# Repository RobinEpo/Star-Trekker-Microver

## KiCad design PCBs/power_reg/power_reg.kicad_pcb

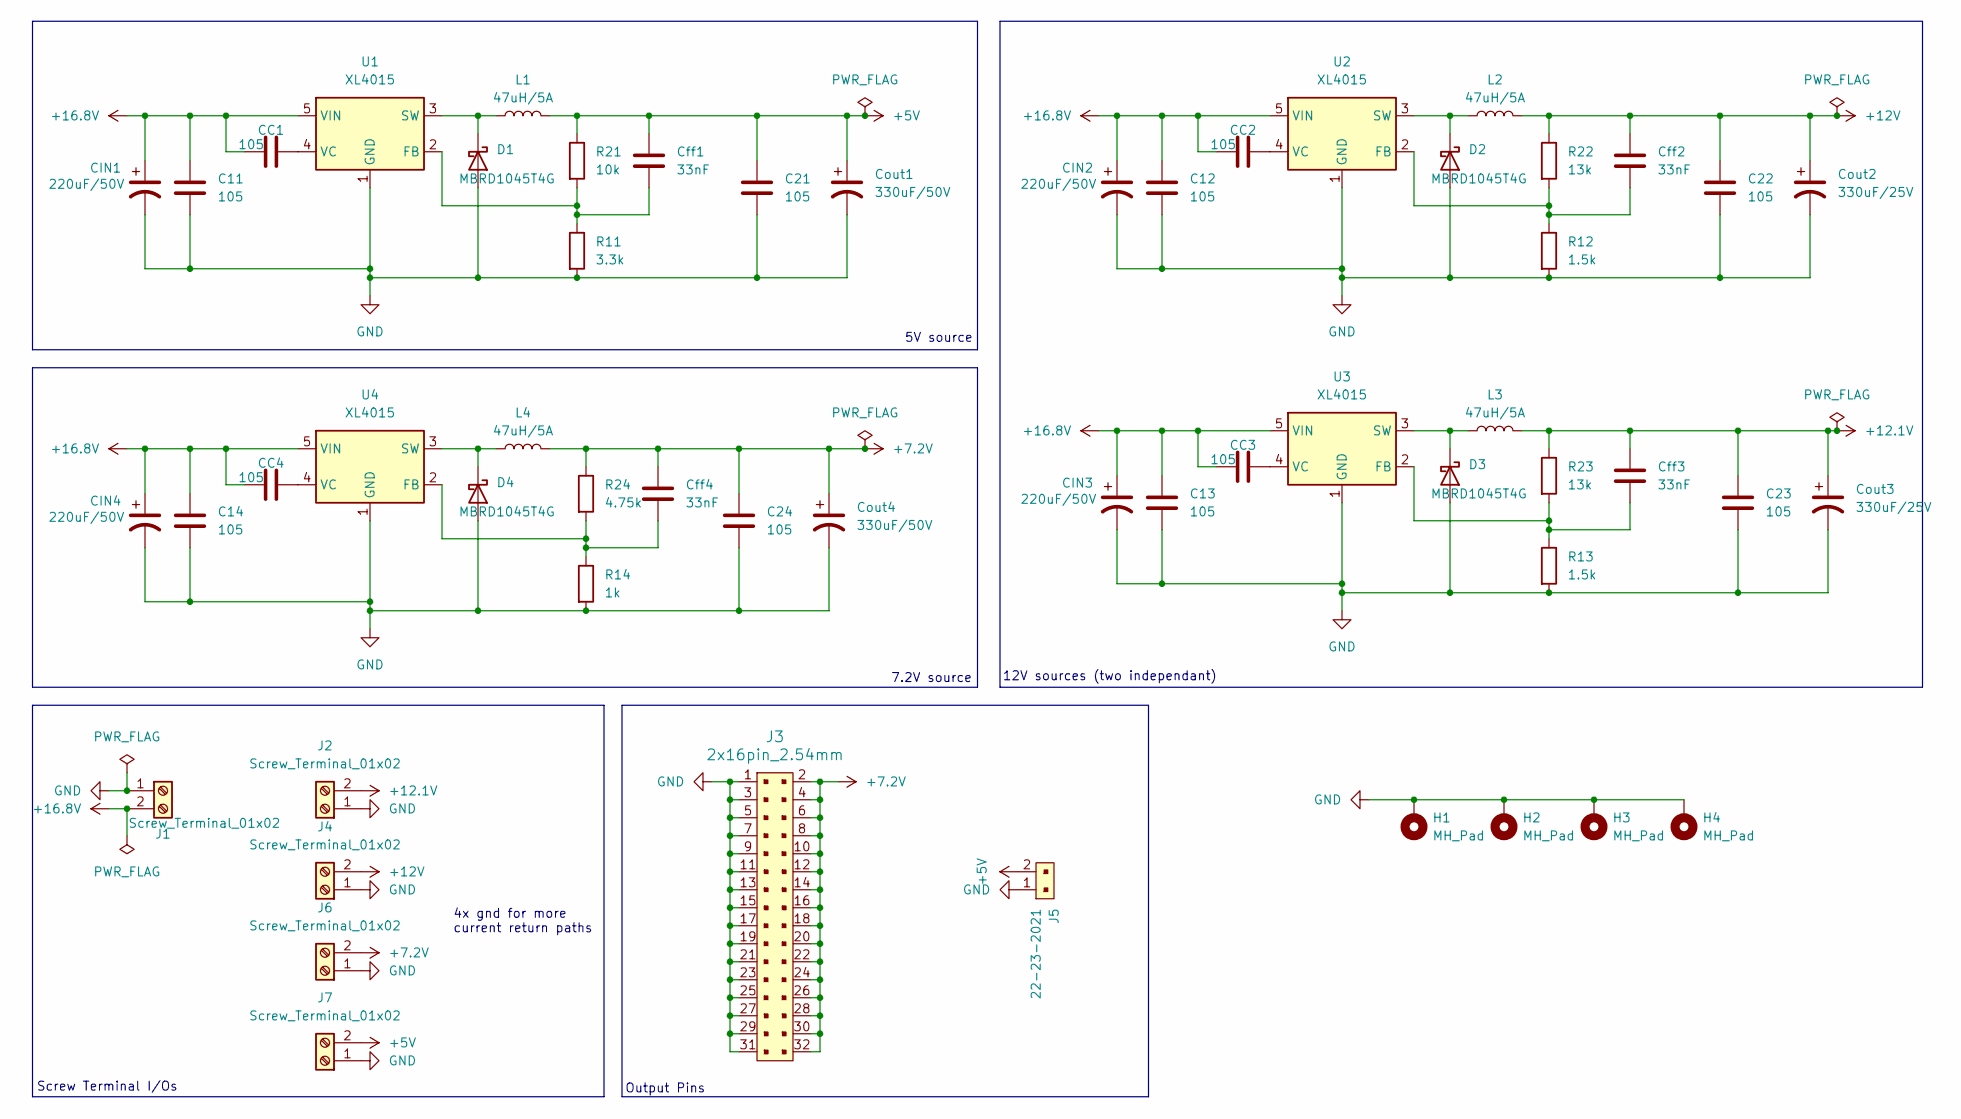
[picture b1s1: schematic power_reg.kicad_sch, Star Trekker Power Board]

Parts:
C11, C12, C13, C14, C21, C22, C23, C24: 105; C_0805_2012Metric_Pad1.18x1.45mm_HandSolder
CC1, CC2, CC3, CC4: 105; C_0805_2012Metric_Pad1.18x1.45mm_HandSolder
CIN1, CIN2, CIN3, CIN4: 220uF/50V; CP_Elec_10x10.5
Cff1, Cff2, Cff3, Cff4: 33nF; C_0603_1608Metric_Pad1.08x0.95mm_HandSolder
Cout1, Cout4: 330uF/50V; CP_Elec_10x10.5
Cout2, Cout3: 330uF/25V; CP_Elec_10x10.5
D1, D2, D3, D4: MBRD1045T4G; TO-252-2
H1, H2, H3, H4: MH_Pad; MountingHole_3.2mm_M3_DIN965_Pad
J1, J2, J4, J6, J7: Screw_Terminal_01x02; TerminalBlock_Phoenix_PT-1,5-2-5.0-H_1x02_P5.00mm_Horizontal
J3: 2x16pin_2.54mm; PinHeader_2x16_P2.54mm_Vertical; MPN 3220-10-0100-00; Digi-Key_PN 1175-1627-ND
J5: 22-23-2021; PinHeader_1x2_P2.54mm_Drill1.02mm; MPN 22-23-2021; Digi-Key_PN WM4200-ND
L1, L2, L3, L4: 47uH/5A; L_13.8x12.6mm_H6.5mm
R11: 3.3k; R_0805_2012Metric_Pad1.20x1.40mm_HandSolder
R12, R13: 1.5k; R_0805_2012Metric_Pad1.20x1.40mm_HandSolder
R14: 1k; R_0805_2012Metric_Pad1.20x1.40mm_HandSolder
R21: 10k; R_0805_2012Metric_Pad1.20x1.40mm_HandSolder
R22, R23: 13k; R_0805_2012Metric_Pad1.20x1.40mm_HandSolder
R24: 4.75k; R_0805_2012Metric_Pad1.20x1.40mm_HandSolder
U1, U2, U3, U4: XL4015; TO-263-5_TabPin3

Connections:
+5V: C21.1, Cff1.1, Cout1.1, J5.2, J7.2, L1.2, R21.1
+7.2V: C24.1, Cff4.1, Cout4.1, J3.2, J3.4, J3.6, J3.8, J3.10, J3.12, J3.14, J3.16, J3.18, J3.20, J3.22, J3.24, J3.26, J3.28, J3.30, J3.32, J6.2, L4.2, R24.1
+12.1V: C23.1, Cff3.1, Cout3.1, J2.2, L3.2, R23.1
+12V: C22.1, Cff2.1, Cout2.1, J4.2, L2.2, R22.1
+16.8V: C11.1, C12.1, C13.1, C14.1, CC1.1, CC2.1, CC3.1, CC4.1, CIN1.1, CIN2.1, CIN3.1, CIN4.1, J1.2, U1.5 (VIN), U2.5 (VIN), U3.5 (VIN), U4.5 (VIN)
GND: C11.2, C12.2, C13.2, C14.2, C21.2, C22.2, C23.2, C24.2, CIN1.2, CIN2.2, CIN3.2, CIN4.2, Cout1.2, Cout2.2, Cout3.2, Cout4.2, D1.1 (A), D2.1 (A), D3.1 (A), D4.1 (A), H1.1, H2.1, H3.1, H4.1, J1.1, J2.1, J3.1, J3.3, J3.5, J3.7, J3.9, J3.11, J3.13, J3.15, J3.17, J3.19, J3.21, J3.23, J3.25, J3.27, J3.29, J3.31, J4.1, J5.1, J6.1, J7.1, R11.2, R12.2, R13.2, R14.2, U1.1 (GND), U2.1 (GND), U3.1 (GND), U4.1 (GND)
unnamed: D1.2 (K), L1.1, U1.3 (SW)
unnamed: D2.2 (K), L2.1, U2.3 (SW)
unnamed: D3.2 (K), L3.1, U3.3 (SW)
unnamed: D4.2 (K), L4.1, U4.3 (SW)
unnamed: Cff1.2, R11.1, R21.2, U1.2 (FB)
unnamed: CC1.2, U1.4 (VC)
unnamed: Cff2.2, R12.1, R22.2, U2.2 (FB)
unnamed: CC2.2, U2.4 (VC)
unnamed: Cff3.2, R13.1, R23.2, U3.2 (FB)
unnamed: CC3.2, U3.4 (VC)
unnamed: Cff4.2, R14.1, R24.2, U4.2 (FB)
unnamed: CC4.2, U4.4 (VC)

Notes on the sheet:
Output Pins
5V source
Screw Terminal I/Os
7.2V source
12V sources (two independant)
4x gnd for more current return paths

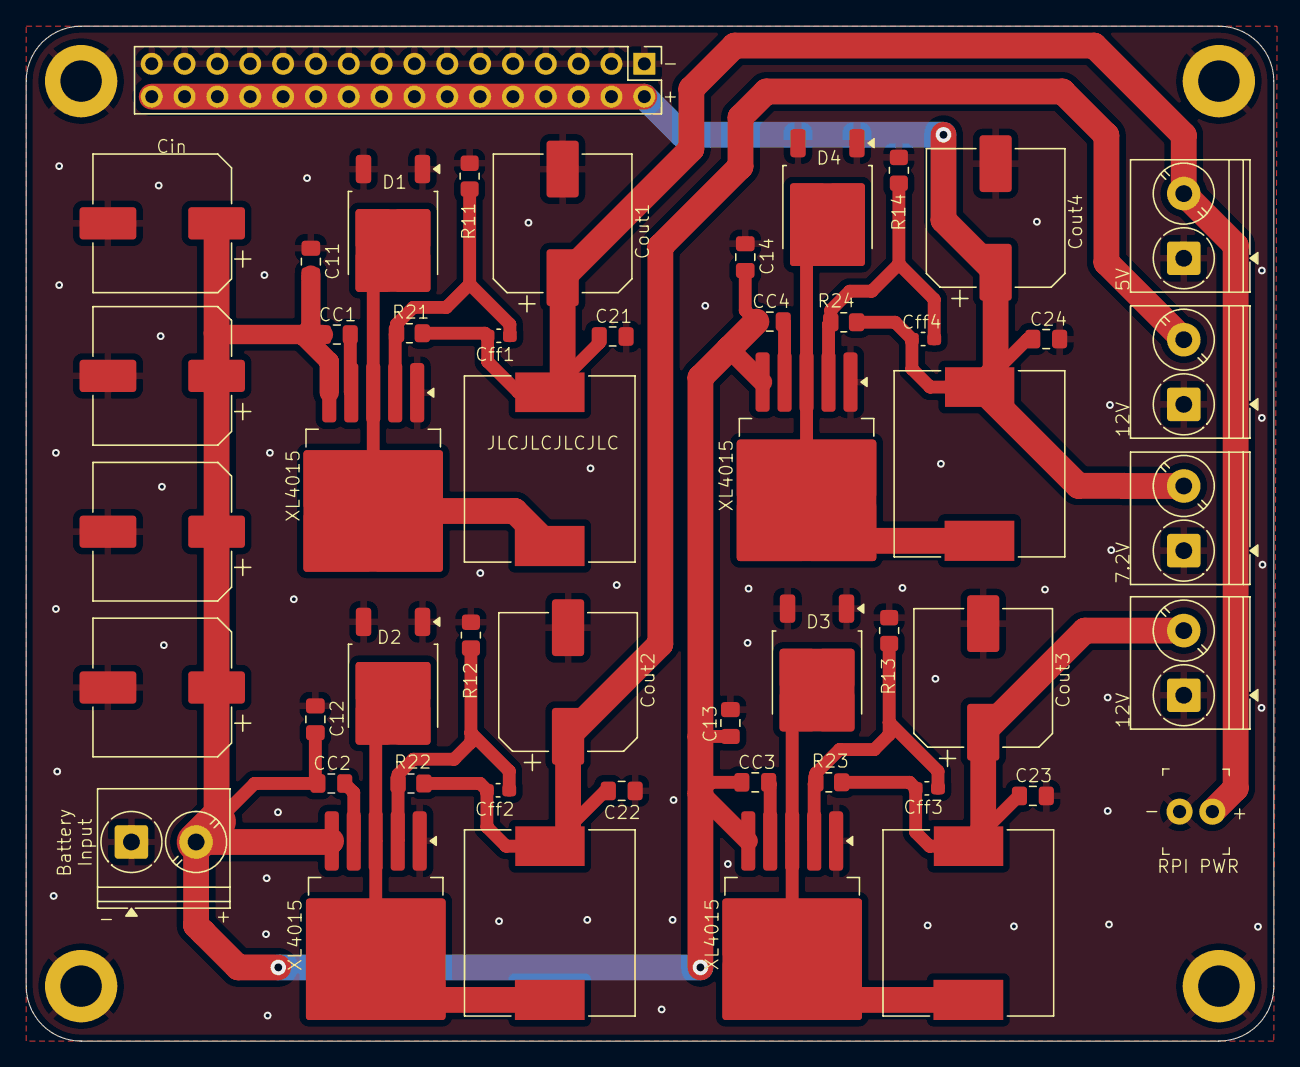
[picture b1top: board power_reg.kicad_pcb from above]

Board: 2 copper layers, 96.5 x 78.5 mm, 55 parts (0 on the bottom side), 18 nets.

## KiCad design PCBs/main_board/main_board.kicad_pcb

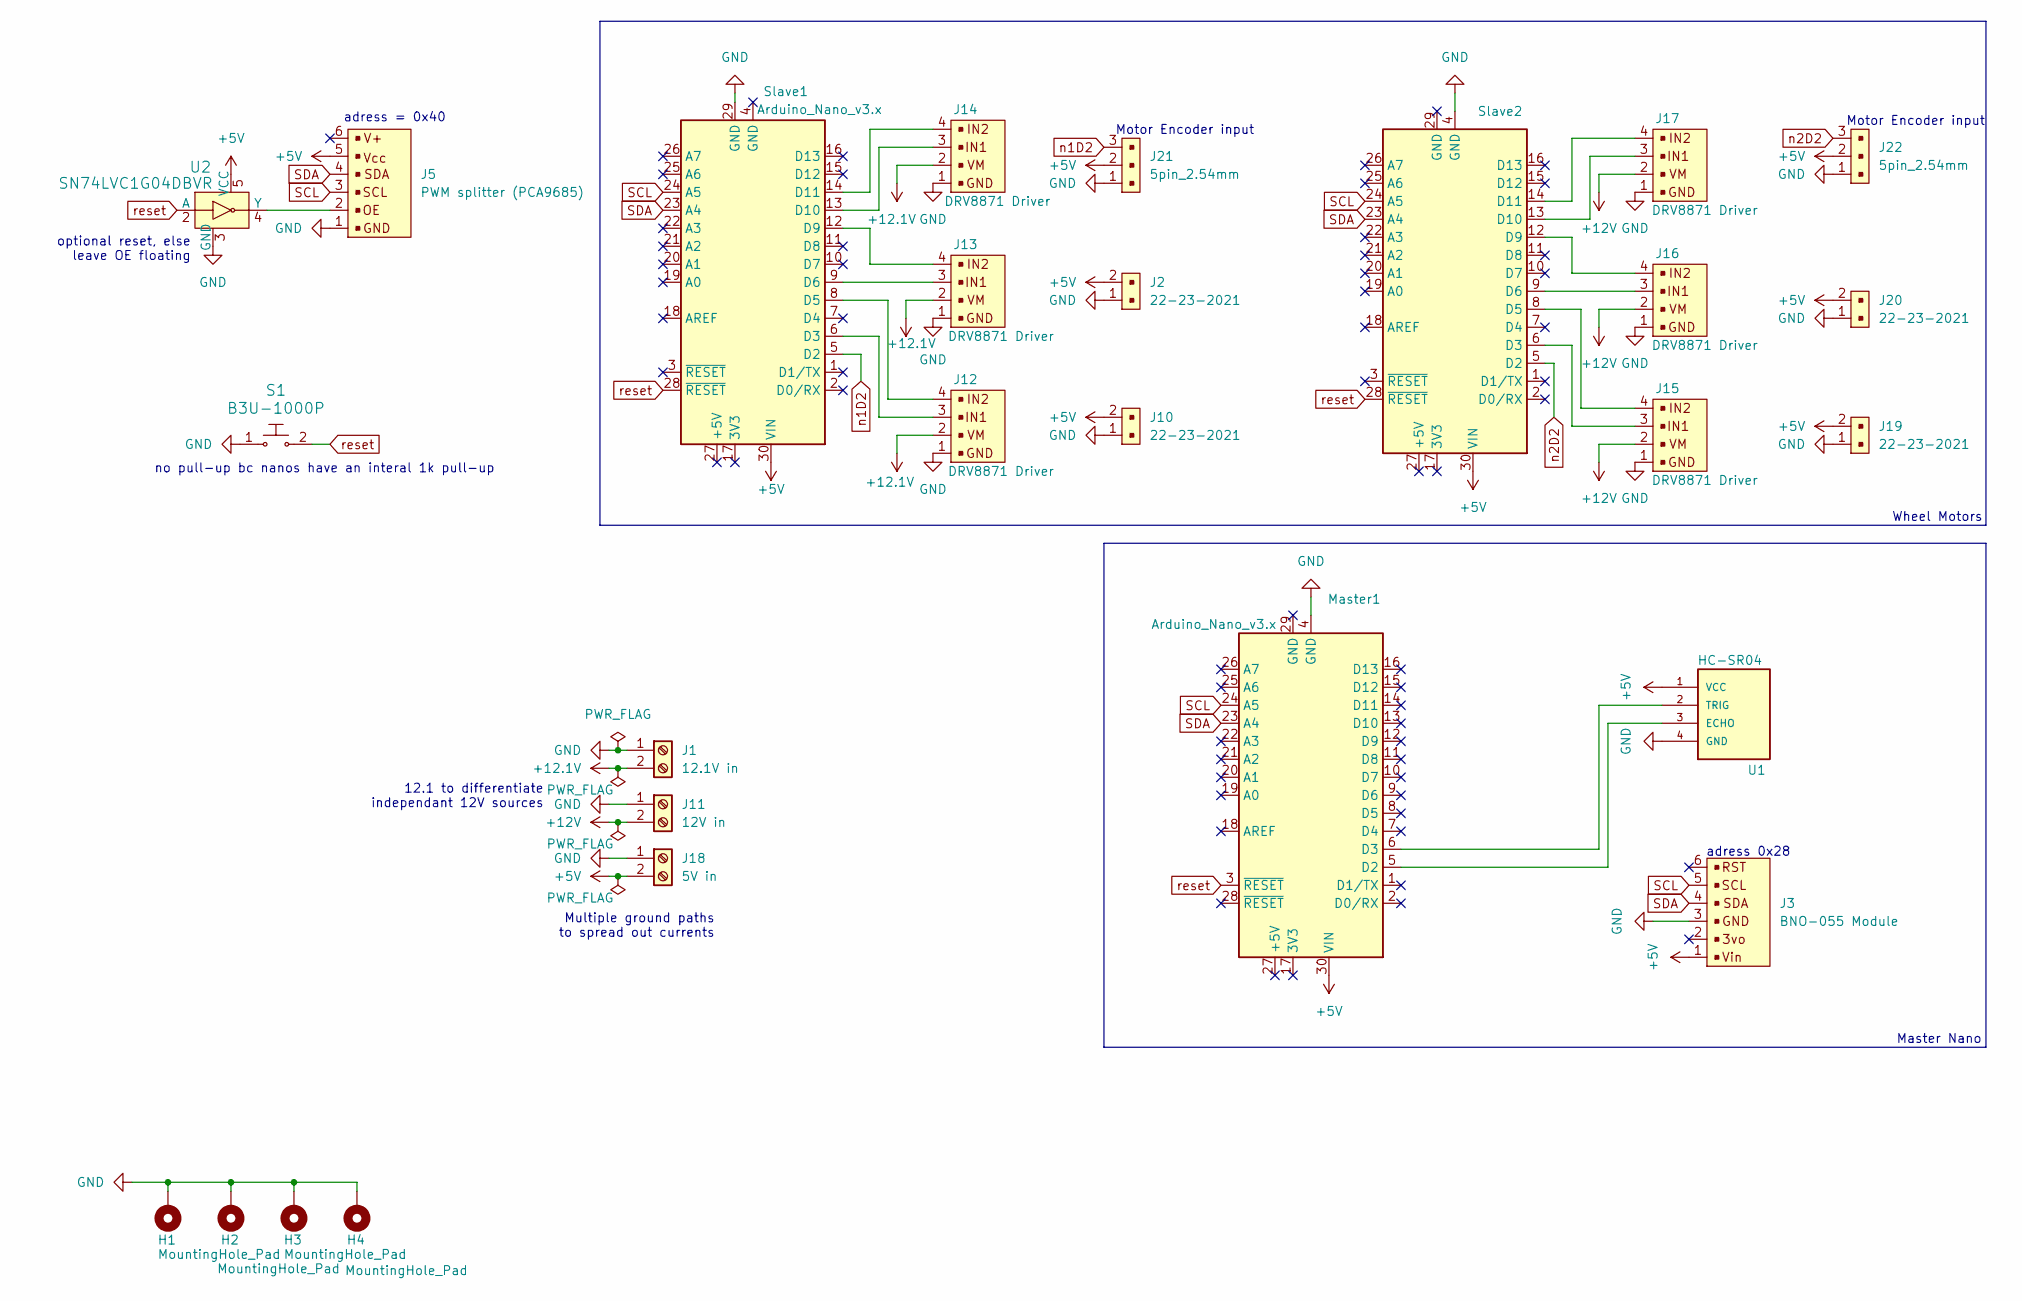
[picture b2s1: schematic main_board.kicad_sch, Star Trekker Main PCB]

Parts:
H1, H2, H3, H4: MountingHole_Pad; MountingHole_3.2mm_M3_Pad
J1: 12.1V in; TerminalBlock_Phoenix_PT-1,5-2-3.5-H_1x02_P3.50mm_Horizontal
J2, J10, J19, J20: 22-23-2021; PinHeader_1x2_P2.54mm_Drill1.02mm; MPN 22-23-2021; Digi-Key_PN WM4200-ND
J3: BNO-055 Module; my_6pin_2_frown; MPN B4B-XH-A(LF)(SN); Digi-Key_PN 455-2249-ND
J5: PWM splitter (PCA9685); my_6pin_2_frown; MPN B4B-XH-A(LF)(SN); Digi-Key_PN 455-2249-ND
J11: 12V in; TerminalBlock_Phoenix_PT-1,5-2-3.5-H_1x02_P3.50mm_Horizontal
J12, J13, J14, J15, J16, J17: DRV8871 Driver; PinHeader_1x4_P2.54mm_Drill1.02mm; MPN B4B-XH-A(LF)(SN); Digi-Key_PN 455-2249-ND
J18: 5V in; TerminalBlock_Phoenix_PT-1,5-2-3.5-H_1x02_P3.50mm_Horizontal
J21, J22: 5pin_2.54mm; PinHeader_1x3_P2.54mm_Drill1.02mm_1; MPN B5B-XH-A(LF)(SN); Digi-Key_PN 455-2270-ND
Master1: Arduino_Nano_v3.x; Arduino_Nano
S1: B3U-1000P; Switch_Tactile_SMD_B3U-1000P; MPN B3U-1000P; Digi-Key_PN SW1020CT-ND
Slave1, Slave2: Arduino_Nano_v3.x; Arduino_Nano
U1: HC-SR04; HC_SR-04_only_pins
U2: SN74LVC1G04DBVR; SOT-753; MPN SN74LVC1G04DBVR; Digi-Key_PN 296-11599-1-ND

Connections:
+5V: J2.2, J3.1, J5.5, J10.2, J18.2, J19.2, J20.2, J21.2, J22.2, Master1.30 (VIN), Slave1.30 (VIN), Slave2.30 (VIN), U1.1 (VCC), U2.5 (VCC)
+12.1V: J1.2, J12.2, J13.2, J14.2
+12V: J11.2, J15.2, J16.2, J17.2
GND: H1.1, H2.1, H3.1, H4.1, J1.1, J2.1, J3.3, J5.1, J10.1, J11.1, J12.1, J13.1, J14.1, J15.1, J16.1, J17.1, J18.1, J19.1, J20.1, J21.1, J22.1, Master1.4 (GND), S1.1, Slave1.29 (GND), Slave2.4 (GND), U1.4 (GND), U2.3 (GND)
unnamed: Master1.5 (D2), U1.3 (ECHO)
unnamed: Master1.6 (D3), U1.2 (TRIG)
unnamed: J12.3, Slave1.6 (D3)
unnamed: J12.4, Slave1.8 (D5)
unnamed: J13.3, Slave1.9 (D6)
unnamed: J13.4, Slave1.12 (D9)
unnamed: J14.3, Slave1.13 (D10)
unnamed: J14.4, Slave1.14 (D11)
unnamed: J15.3, Slave2.6 (D3)
unnamed: J15.4, Slave2.8 (D5)
unnamed: J16.3, Slave2.9 (D6)
unnamed: J16.4, Slave2.12 (D9)
unnamed: J17.3, Slave2.13 (D10)
unnamed: J17.4, Slave2.14 (D11)
unnamed: J5.2, U2.4 (Y)
SCL: J3.5, J5.3, Master1.24 (A5), Slave1.24 (A5), Slave2.24 (A5)
SDA: J3.4, J5.4, Master1.23 (A4), Slave1.23 (A4), Slave2.23 (A4)
n1D2: J21.3, Slave1.5 (D2)
n2D2: J22.3, Slave2.5 (D2)
reset: Master1.3 (~RESET), S1.2, Slave1.28 (~RESET), Slave2.28 (~RESET), U2.2 (A)

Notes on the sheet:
Motor Encoder input
adress = 0x40
no pull-up bc nanos have an interal 1k pull-up
12.1 to differentiate independant 12V sources
Wheel Motors
adress 0x28
Master Nano
Multiple ground paths to spread out currents
optional reset, else leave OE floating

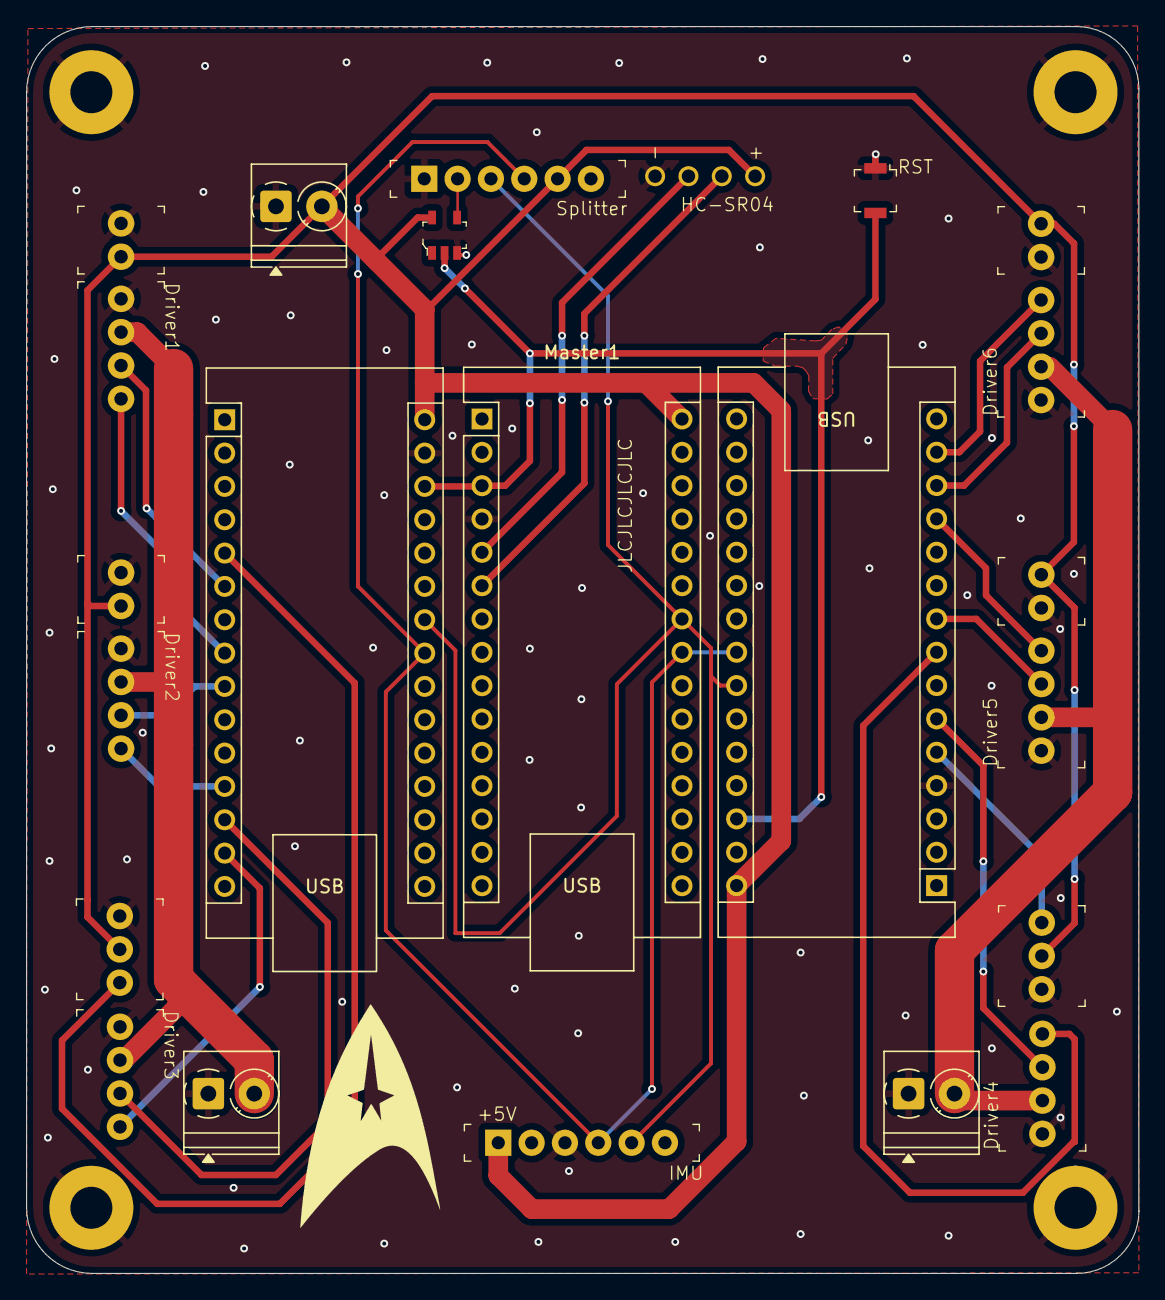
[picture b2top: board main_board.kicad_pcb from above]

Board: 2 copper layers, 84.8 x 95.0 mm, 27 parts (0 on the bottom side), 24 nets.

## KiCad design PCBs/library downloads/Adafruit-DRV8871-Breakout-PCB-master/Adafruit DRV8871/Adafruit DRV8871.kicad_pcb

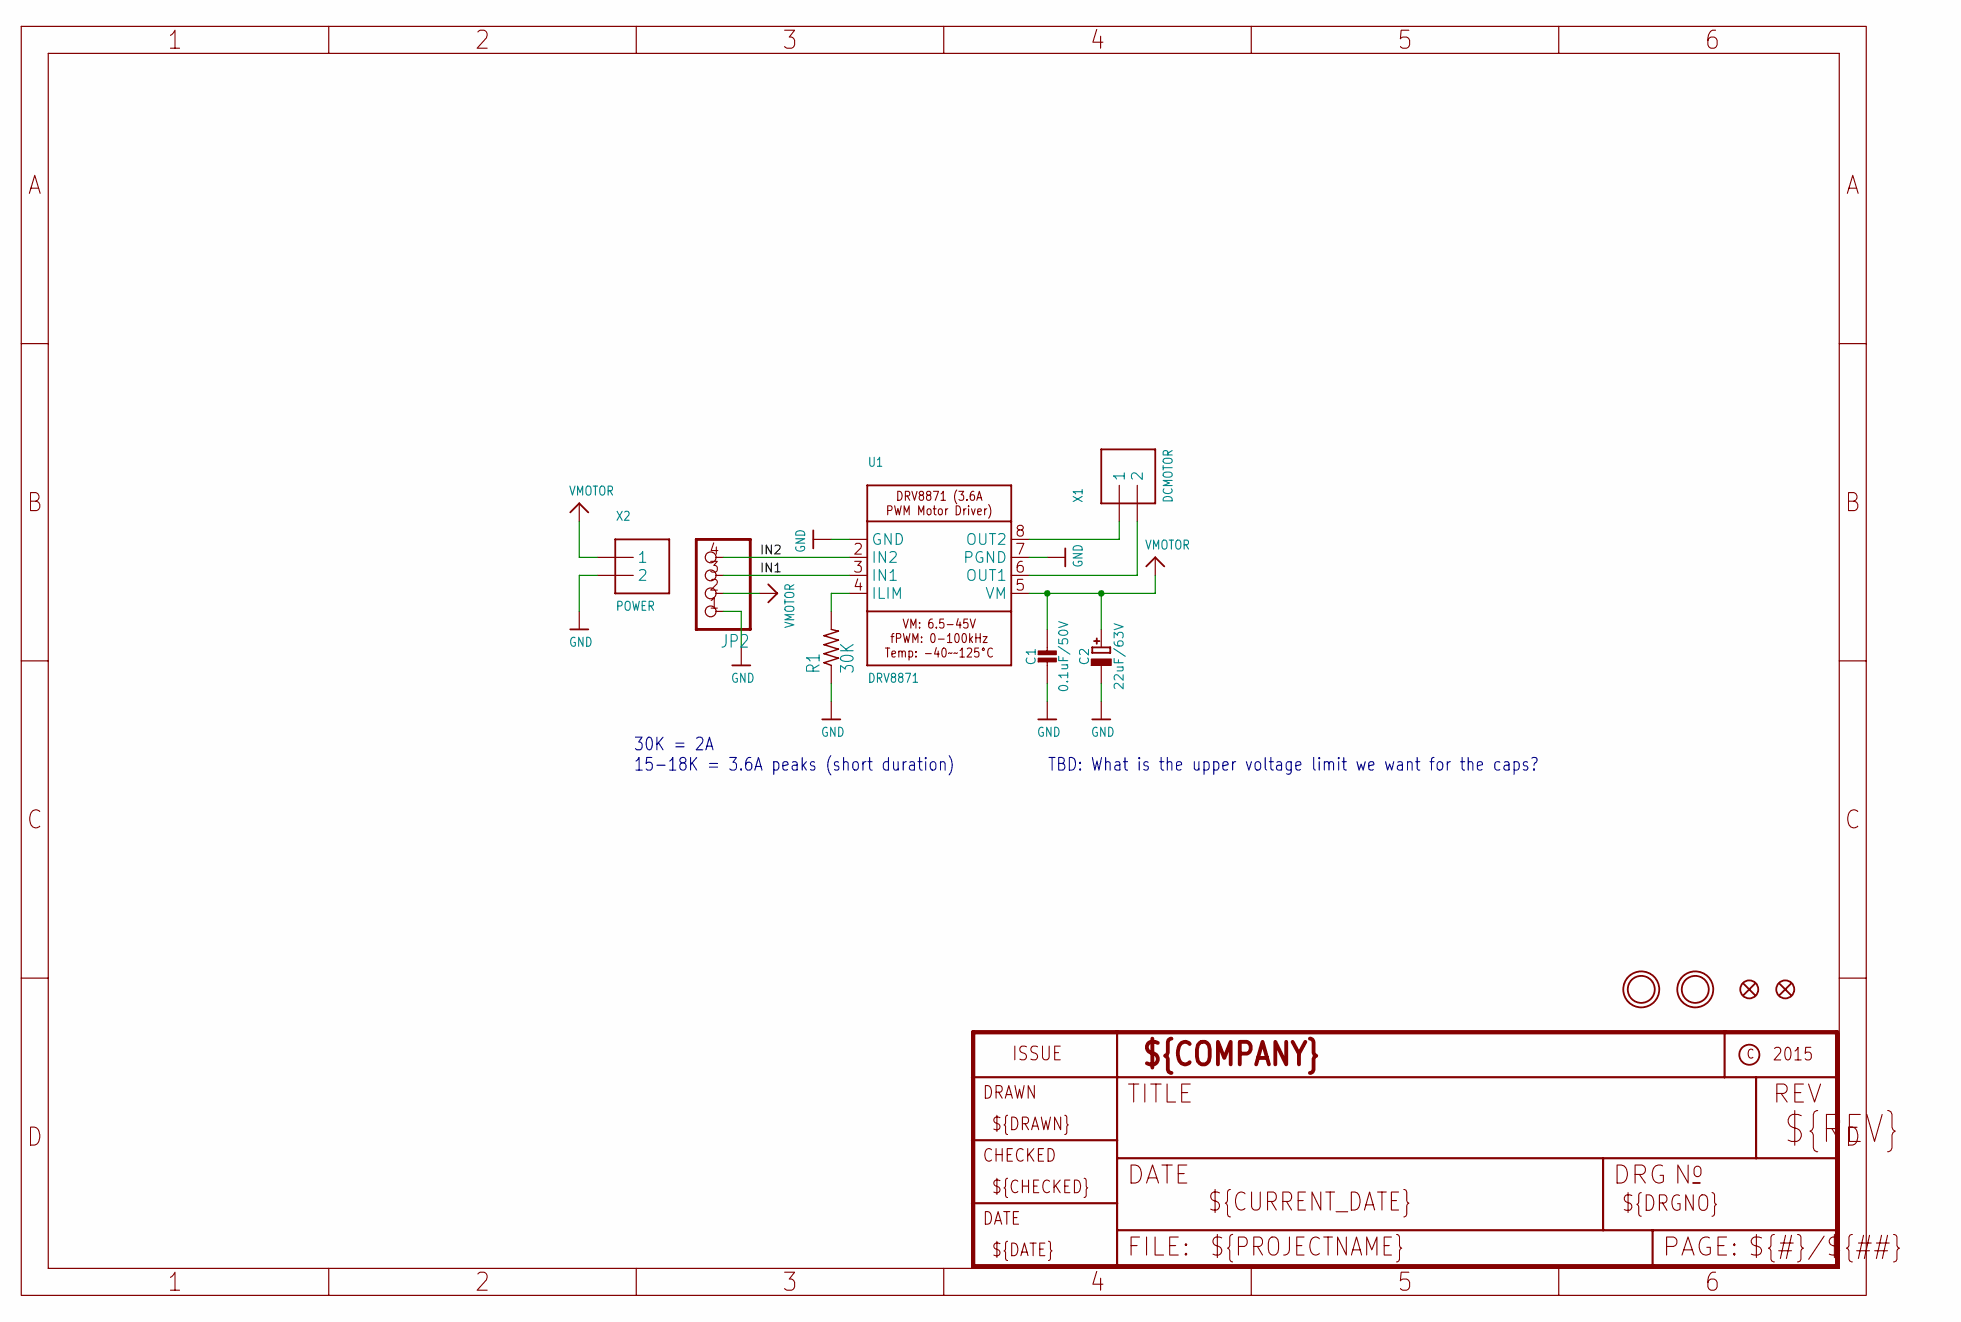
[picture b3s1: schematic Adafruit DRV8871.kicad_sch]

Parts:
C1: 0.1uF/50V; 0805-NO
C2: 22uF/63V; PANASONIC_D
FID1, FID2: FIDUCIAL""; FIDUCIAL_1MM
JP2: HEADER-1X476MIL; 1X04_ROUND_76
R1: 30K; 0805-THM
U1: DRV8871; HSOP8
U$9, U$10: MOUNTINGHOLE2.5; MOUNTINGHOLE_2.5_PLATED
X1: DCMOTOR; TERMBLOCK_1X2-3.5MM
X2: POWER; TERMBLOCK_1X2-3.5MM

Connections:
GND: C1.2, C2.-, JP2.1, R1.1, U1.1 (GND), U1.7 (PGND), U1.GND, U1.P$1 (GND), U1.P$2 (GND), U1.P$3 (GND), U1.P$4 (GND), X2.2
IN1: JP2.3, U1.3 (IN1)
IN2: JP2.4, U1.2 (IN2)
unnamed: R1.2, U1.4 (ILIM)
OUT1: U1.6 (OUT1), X1.2
OUT2: U1.8 (OUT2), X1.1
VMOTOR: C1.1, C2.+, JP2.2, U1.5 (VM), X2.1

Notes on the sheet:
TBD: What is the upper voltage limit we want for the caps?
30K = 2A 15-18K = 3.6A peaks (short duration~{})

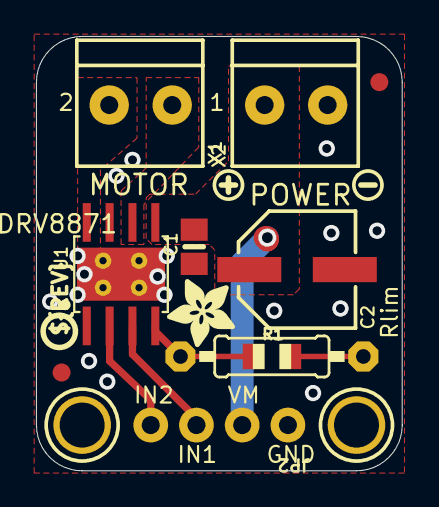
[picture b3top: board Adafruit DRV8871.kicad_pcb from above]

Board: 2 copper layers, 20.3 x 24.1 mm, 15 parts (0 on the bottom side), 7 nets.

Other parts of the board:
U$11: SYMBOL_PLUS
U$12: SYMBOL_MINUS
U$14: ADAFRUIT_3.5MM
U$15: PCBFEAT-REV-040

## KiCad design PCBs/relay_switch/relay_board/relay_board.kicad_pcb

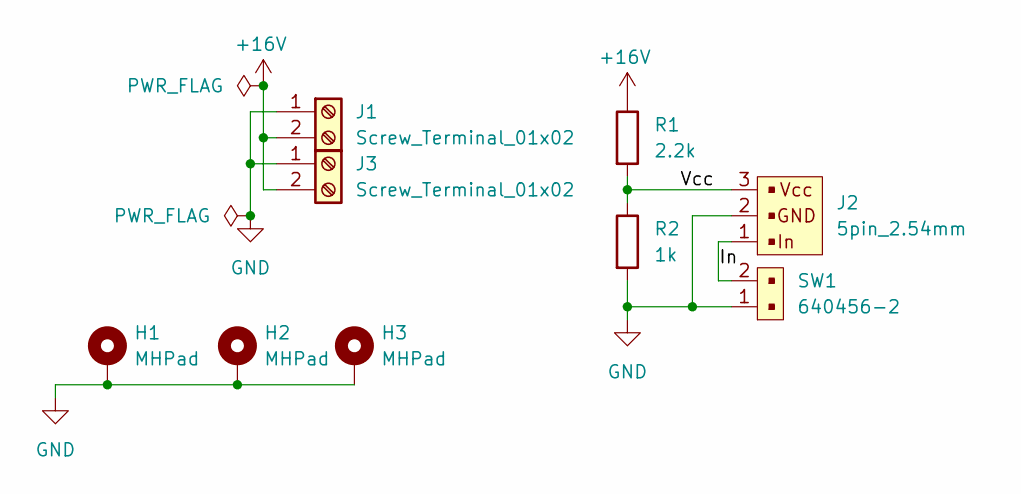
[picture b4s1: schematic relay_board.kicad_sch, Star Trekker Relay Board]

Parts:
H1, H2, H3: MHPad; MountingHole_3.2mm_M3_DIN965_Pad
J1, J3: Screw_Terminal_01x02; TerminalBlock_Phoenix_PT-1,5-2-5.0-H_1x02_P5.00mm_Horizontal
J2: 5pin_2.54mm; PinHeader_1x3_P2.54mm_Drill1.02mm_1; MPN B5B-XH-A(LF)(SN); Digi-Key_PN 455-2270-ND
R1: 2.2k; R_0603_1608Metric_Pad0.98x0.95mm_HandSolder
R2: 1k; R_0603_1608Metric_Pad0.98x0.95mm_HandSolder
SW1: 640456-2; PinHeader_1x2_P2.54mm_Drill1.02mm; MPN 640456-2; Digi-Key_PN A1921-ND

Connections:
+16V: J1.2, J3.2, R1.1
/In: J2.1, SW1.2
/Vcc: J2.3, R1.2, R2.1
GND: H1.1, H2.1, H3.1, J1.1, J2.2, J3.1, R2.2, SW1.1

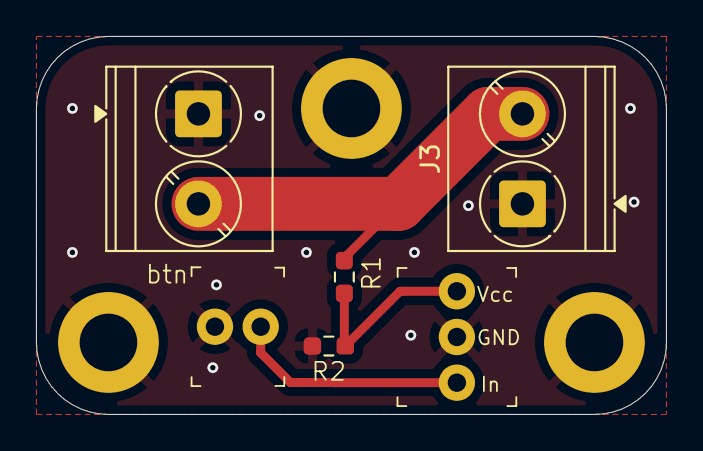
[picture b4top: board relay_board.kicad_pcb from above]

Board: 2 copper layers, 35.0 x 21.0 mm, 9 parts (0 on the bottom side), 4 nets.

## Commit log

2025-04-08 first camera test with godot
2025-05-07 Direction adaptation
2025-05-09 Create PCBs folder
2025-05-09 Added the PCBs folders, including the v2.0 of the power_reg but otherwise is just the v1.0s
2025-05-11 Added v1.1 of arduinos codes
2025-05-11 Added code folder and no_conn.py
2025-05-11 updated no laptop
2025-05-11 State of code after leaving robop on sunday of review
2025-05-11 Mati night edits - Big simplifcations in arduino codes and verified rpi to master comms
2025-05-11 same as before
2025-05-12 Premier code pour faire fonctionner le bras
2025-05-12 Correction 2/3 bugs + debuggage léger
    Il faudra juste ne pas oublier de supprimer les lignes inutiles de print. Elles peuvent tjrs servir entre temps.
2025-05-14 Correction angles / variables globales
2025-05-14 Rajout boutons mode / boost
2025-05-15 Add values and correct transmission
2025-05-15 Modified Arduino code to one that's simpler and tested works!
2025-05-15 fixed float
2025-05-15 changed delay
2025-05-15 added temp.py
2025-05-17 unimportant
2025-05-17 simple file transfer
2025-05-17 Changed values to X mode
2025-05-17 nothin
2025-05-17 fixed back values mistake, other mistake still pending
2025-05-19 minor changes
2025-05-21 Nouvelle version des codes (complétée avec bras)
2025-05-23 added files for rpi to pc comm
2025-05-23 Added sensor receiver
2025-05-23 Reorganizing
2025-05-23 still orga
2025-05-23 added rpi comm file
2025-05-24 small changes
2025-05-24 Added shell scripts
2025-05-24 updated ip
2025-05-24 idek
2025-05-24 restablished comm.py as com.py
2025-05-24 added gpt_com.py
2025-05-24 changed refresh rate
2025-05-24 2nd gpt code
2025-05-24 Changed all IPs to local
2025-05-24 added both local and phone version
2025-05-24 minor error fix
2025-05-24 fixed angle(s)
2025-05-24 changed to udp hopefully
